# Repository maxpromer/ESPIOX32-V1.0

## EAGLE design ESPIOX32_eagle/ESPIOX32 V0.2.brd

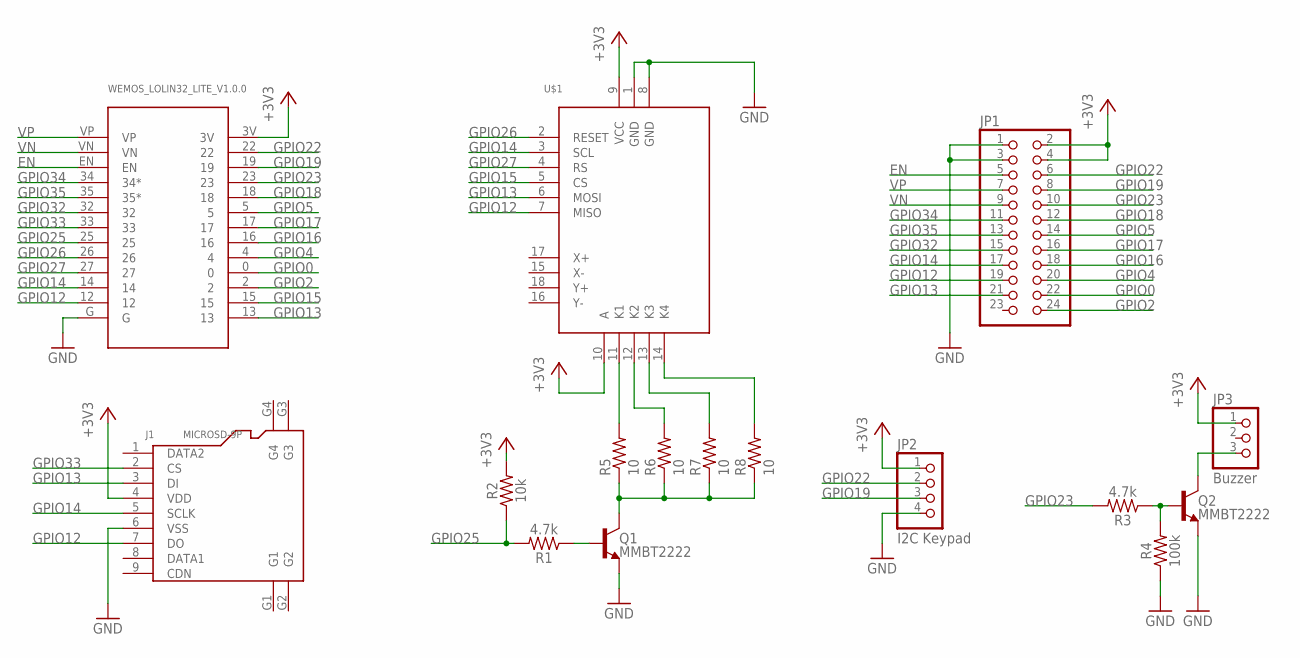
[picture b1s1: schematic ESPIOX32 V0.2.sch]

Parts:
J1: MICROSD-9P; MICRO-SD9+4P-SMD-16.1X14.5X1.85MM
JP1: PINHD-2X12_2.54-SMD; 2X12SMD
JP2: I2C Keypad; 1X04SMD/90
JP3: Buzzer; 1X03SMD/90
Q1, Q2: MMBT2222; SOT23-3
R1, R3: 4.7k; 0603
R2: 10k; 0603
R4: 100k; 0603
R5, R6, R7, R8: 10; 0603-RES
U$1: 18P_3.2IN_TFT_LCD; 18PIN_TFTLCD
WEMOS_LOLIN32_LITE_V1.0.0: WEMOS_LOLIN32_LITE_V1.0.0

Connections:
+3V3: J1.4 (VDD), JP1.2, JP1.4, JP2.1, JP3.1, R2.2, U$1.9 (VCC), U$1.10 (A), WEMOS_LOLIN32_LITE_V1.0.0.3V
EN: JP1.5, WEMOS_LOLIN32_LITE_V1.0.0.EN
GND: J1.6 (VSS), JP1.1, JP1.3, JP2.4, Q1.2 (E), Q2.2 (E), R4.1, U$1.1 (GND), U$1.8 (GND), WEMOS_LOLIN32_LITE_V1.0.0.G
GPIO0: JP1.22, WEMOS_LOLIN32_LITE_V1.0.0.0
GPIO2: JP1.24, WEMOS_LOLIN32_LITE_V1.0.0.2
GPIO4: JP1.20, WEMOS_LOLIN32_LITE_V1.0.0.4
GPIO5: JP1.14, WEMOS_LOLIN32_LITE_V1.0.0.5
GPIO12: J1.7 (DO), JP1.19, U$1.7 (MISO), WEMOS_LOLIN32_LITE_V1.0.0.12
GPIO13: J1.3 (DI), JP1.21, U$1.6 (MOSI), WEMOS_LOLIN32_LITE_V1.0.0.13
GPIO14: J1.5 (SCLK), JP1.17, U$1.3 (SCL), WEMOS_LOLIN32_LITE_V1.0.0.14
GPIO15: U$1.5 (CS), WEMOS_LOLIN32_LITE_V1.0.0.15
GPIO16: JP1.18, WEMOS_LOLIN32_LITE_V1.0.0.16
GPIO17: JP1.16, WEMOS_LOLIN32_LITE_V1.0.0.17
GPIO18: JP1.12, WEMOS_LOLIN32_LITE_V1.0.0.18
GPIO19: JP1.8, JP2.3, WEMOS_LOLIN32_LITE_V1.0.0.19
GPIO22: JP1.6, JP2.2, WEMOS_LOLIN32_LITE_V1.0.0.22
GPIO23: JP1.10, R3.2, WEMOS_LOLIN32_LITE_V1.0.0.23
GPIO25: R1.2, R2.1, WEMOS_LOLIN32_LITE_V1.0.0.25
GPIO26: U$1.2 (RESET), WEMOS_LOLIN32_LITE_V1.0.0.26
GPIO27: U$1.4 (RS), WEMOS_LOLIN32_LITE_V1.0.0.27
GPIO32: JP1.15, WEMOS_LOLIN32_LITE_V1.0.0.32
GPIO33: J1.2 (CS), WEMOS_LOLIN32_LITE_V1.0.0.33
GPIO34: JP1.11, WEMOS_LOLIN32_LITE_V1.0.0.34 (34*)
GPIO35: JP1.13, WEMOS_LOLIN32_LITE_V1.0.0.35 (35*)
unnamed: Q1.3 (C), R5.1, R6.1, R7.1, R8.1
unnamed: Q1.1 (B), R1.1
unnamed: Q2.1 (B), R3.1, R4.2
unnamed: JP3.3, Q2.3 (C)
unnamed: R5.2, U$1.11 (K1)
unnamed: R6.2, U$1.12 (K2)
unnamed: R7.2, U$1.13 (K3)
unnamed: R8.2, U$1.14 (K4)
VN: JP1.9, WEMOS_LOLIN32_LITE_V1.0.0.VN
VP: JP1.7, WEMOS_LOLIN32_LITE_V1.0.0.VP

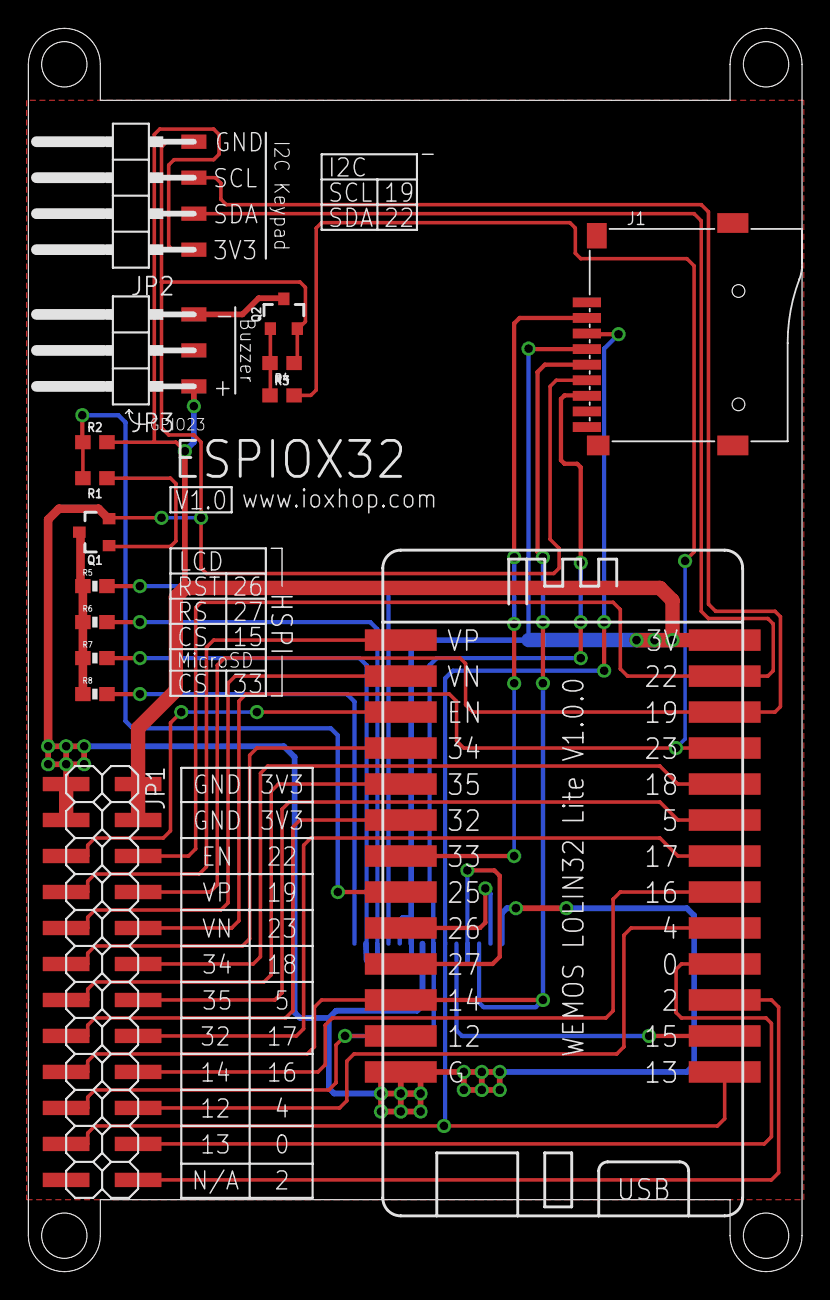
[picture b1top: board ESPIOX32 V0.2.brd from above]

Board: 2 copper layers, 54.6 x 87.8 mm, 16 parts (1 on the bottom side), 34 nets.

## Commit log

2018-02-03 :boom::camel: Added .gitattributes
2018-02-03 hardware

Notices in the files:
parts and their libraries:
SparkFun-DiscreteSemi: Licensing: Creative Commons ShareAlike 4.0 International - https://creativecommons.org/licenses/by-sa/4.0
